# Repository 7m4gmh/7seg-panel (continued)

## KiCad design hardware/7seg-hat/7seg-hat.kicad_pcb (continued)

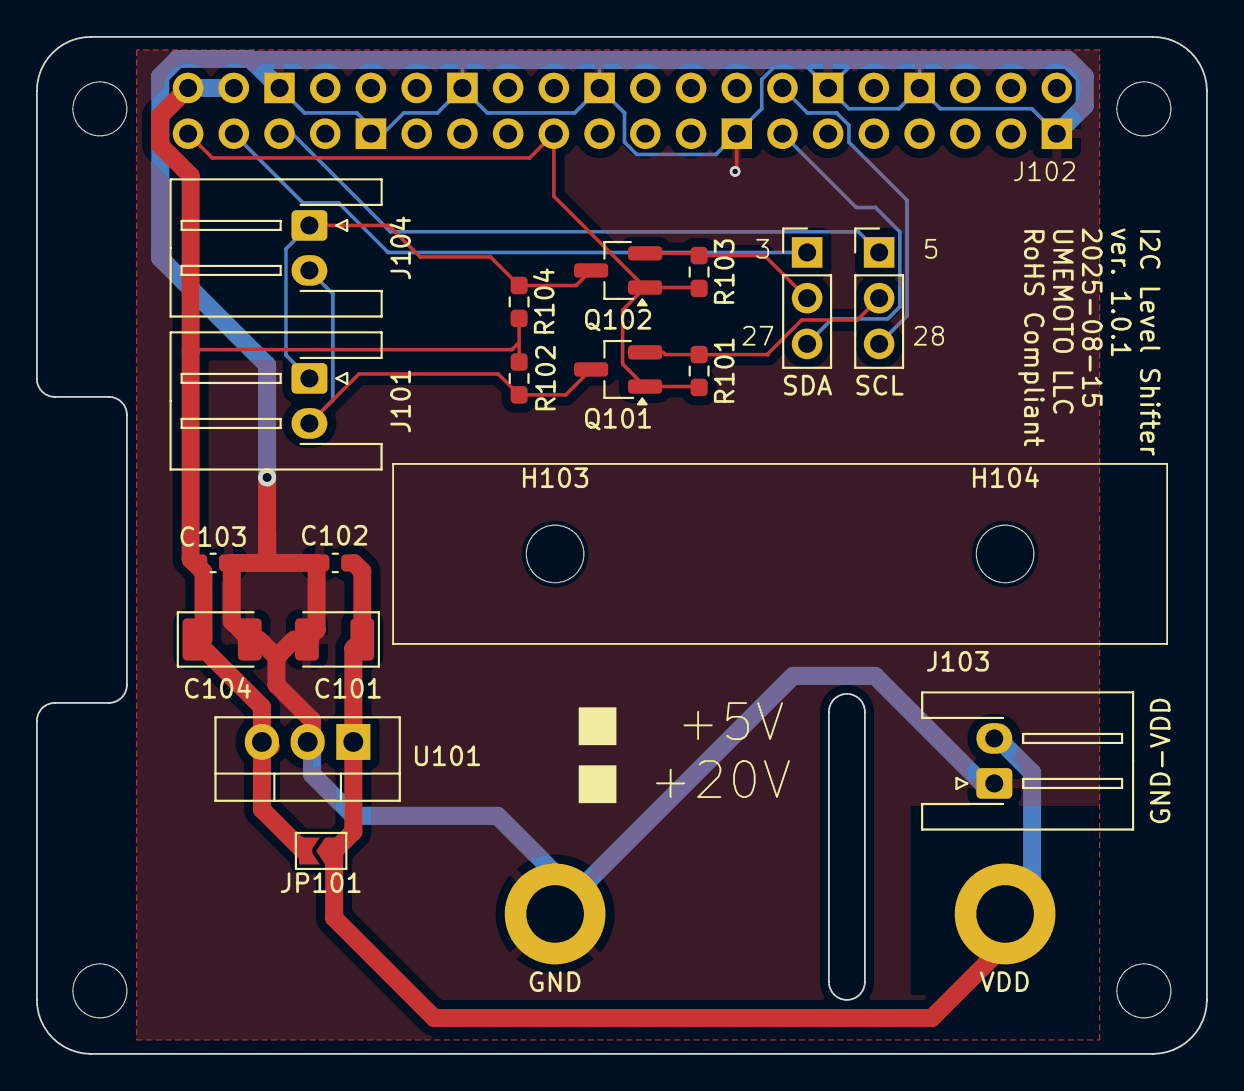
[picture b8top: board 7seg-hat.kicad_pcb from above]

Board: 2 copper layers, 65.0 x 56.5 mm, 22 parts (0 on the bottom side), 12 nets.

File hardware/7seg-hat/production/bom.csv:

Designator,Footprint,Quantity,Value,LCSC Part #
C101,CP_EIA-3528-21_Kemet-B,1,22uF,
C103,0603,1,22uF 6V,
"J101, J104",JST_XH_S2B-XH-A-1_1x02_P2.50mm_Horizontal,2,i2c,
J102,RPI_Hat_B+,1,Raspberry_Pi_4,
J103,JST_XH_S2B-XH-A-1_1x02_P2.50mm_Horizontal,1,GND-VDD,
"Q101, Q102",SOT-23_Handsoldering,2,BSS138,
"R101, R102, R103, R104",0603,4,4k7R,
U101,TO-220-3_Vertical,1,K7805M-2000,
